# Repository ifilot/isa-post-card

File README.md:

# ISA POST card

8-bit ISA post card for XT-class systems

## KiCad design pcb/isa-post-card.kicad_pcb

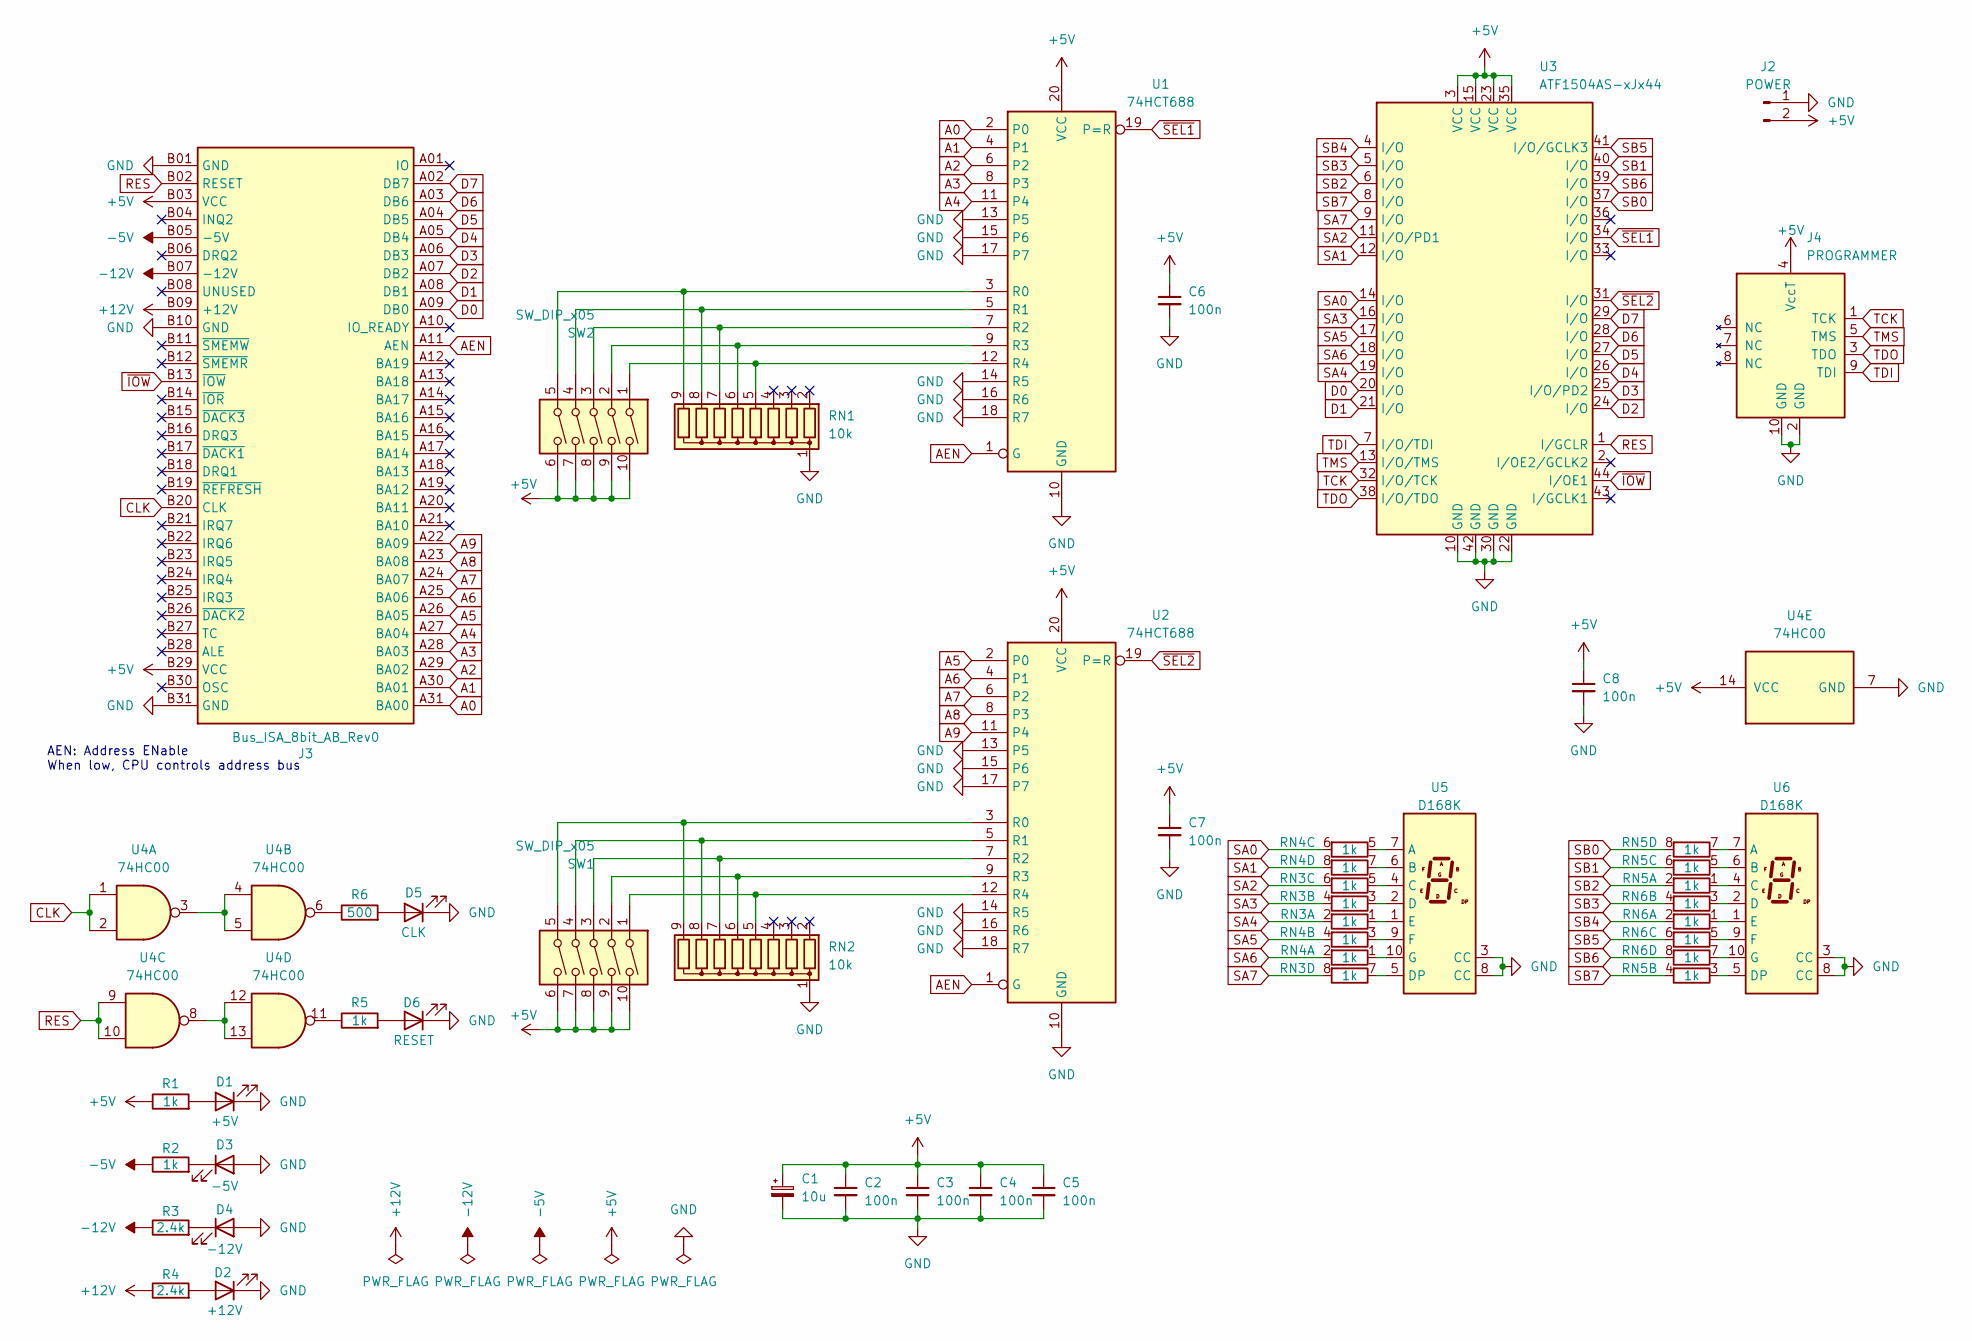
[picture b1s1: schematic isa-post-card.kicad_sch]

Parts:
C1: 10u; CP_Radial_D4.0mm_P1.50mm
C2, C3, C4, C5, C6, C7, C8: 100n; C_Disc_D5.0mm_W2.5mm_P5.00mm
D1: +5V; LED_D5.0mm
D2: +12V; LED_D5.0mm
D3: -5V; LED_D5.0mm
D4: -12V; LED_D5.0mm
D5: CLK; LED_D5.0mm
D6: RESET; LED_D5.0mm
J2: POWER; PinHeader_1x02_P2.54mm_Vertical
J3: Bus_ISA_8bit_AB_Rev0; ISA_CARD_EDGE_CONNECTOR_8BIT_Rev1
J4: PROGRAMMER; IDC-Header_2x05_P2.54mm_Vertical
R1, R2, R5: 1k; R_Axial_DIN0207_L6.3mm_D2.5mm_P7.62mm_Horizontal
R3, R4: 2.4k; R_Axial_DIN0207_L6.3mm_D2.5mm_P7.62mm_Horizontal
R6: 500; R_Axial_DIN0207_L6.3mm_D2.5mm_P7.62mm_Horizontal
RN1, RN2: 10k; R_Array_SIP9
RN3, RN4, RN5, RN6: 1k; R_Array_SIP8
SW1, SW2: SW_DIP_x05; SW_DIP_SPSTx05_Slide_9.78x14.88mm_W7.62mm_P2.54mm
U1, U2: 74HCT688; DIP-20_W7.62mm_Socket
U3: ATF1504AS-xJx44; PLCC-44_THT-Socket
U4: 74HC00; DIP-14_W7.62mm_Socket
U5, U6: D168K; D1X8K

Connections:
+5V: C1.1, C2.1, C3.1, C4.1, C5.1, C6.1, C7.1, C8.1, J2.2, J3.B03 (VCC), J3.B29 (VCC), J4.4 (VccT), R1.1, SW1.6, SW1.7, SW1.8, SW1.9, SW1.10, SW2.6, SW2.7, SW2.8, SW2.9, SW2.10, U1.20 (VCC), U2.20 (VCC), U3.3 (VCC), U3.15 (VCC), U3.23 (VCC), U3.35 (VCC), U4.14 (VCC)
+12V: J3.B09 (+12V), R4.1
-5V: J3.B05 (-5V), R2.1
-12V: J3.B07 (-12V), R3.1
A0: J3.A31 (BA00), U1.2 (P0)
A1: J3.A30 (BA01), U1.4 (P1)
A2: J3.A29 (BA02), U1.6 (P2)
A3: J3.A28 (BA03), U1.8 (P3)
A4: J3.A27 (BA04), U1.11 (P4)
A5: J3.A26 (BA05), U2.2 (P0)
A6: J3.A25 (BA06), U2.4 (P1)
A7: J3.A24 (BA07), U2.6 (P2)
A8: J3.A23 (BA08), U2.8 (P3)
A9: J3.A22 (BA09), U2.11 (P4)
AEN: J3.A11 (AEN), U1.1 (G), U2.1 (G)
CLK: J3.B20 (CLK), U4.1, U4.2
D0: J3.A09 (DB0), U3.20 (I/O)
D1: J3.A08 (DB1), U3.21 (I/O)
D2: J3.A07 (DB2), U3.24 (I/O)
D3: J3.A06 (DB3), U3.25 (I/O/PD2)
D4: J3.A05 (DB4), U3.26 (I/O)
D5: J3.A04 (DB5), U3.27 (I/O)
D6: J3.A03 (DB6), U3.28 (I/O)
D7: J3.A02 (DB7), U3.29 (I/O)
GND: C1.2, C2.2, C3.2, C4.2, C5.2, C6.2, C7.2, C8.2, D1.1 (K), D2.1 (K), D3.2 (A), D4.2 (A), D5.1 (K), D6.1 (K), J2.1, J3.B01 (GND), J3.B10 (GND), J3.B31 (GND), J4.2 (GND), J4.10 (GND), RN1.1 (common), RN2.1 (common), U1.10 (GND), U1.13 (P5), U1.14 (R5), U1.15 (P6), U1.16 (R6), U1.17 (P7), U1.18 (R7), U2.10 (GND), U2.13 (P5), U2.14 (R5), U2.15 (P6), U2.16 (R6), U2.17 (P7), U2.18 (R7), U3.10 (GND), U3.22 (GND), U3.30 (GND), U3.42 (GND), U4.7 (GND), U5.3 (CC), U5.8 (CC), U6.3 (CC), U6.8 (CC)
unnamed: D1.2 (A), R1.2
unnamed: D2.2 (A), R4.2
unnamed: D3.1 (K), R2.2
unnamed: D4.1 (K), R3.2
unnamed: D5.2 (A), R6.2
unnamed: D6.2 (A), R5.2
unnamed: R5.1, U4.11
unnamed: R6.1, U4.6
unnamed: RN1.5 (R4), SW2.1, U1.12 (R4)
unnamed: RN1.6 (R5), SW2.2, U1.9 (R3)
unnamed: RN1.7 (R6), SW2.3, U1.7 (R2)
unnamed: RN1.8 (R7), SW2.4, U1.5 (R1)
unnamed: RN1.9 (R8), SW2.5, U1.3 (R0)
unnamed: RN2.5 (R4), SW1.1, U2.12 (R4)
unnamed: RN2.6 (R5), SW1.2, U2.9 (R3)
unnamed: RN2.7 (R6), SW1.3, U2.7 (R2)
unnamed: RN2.8 (R7), SW1.4, U2.5 (R1)
unnamed: RN2.9 (R8), SW1.5, U2.3 (R0)
unnamed: RN3.1 (R1.1), U5.1 (E)
unnamed: RN3.3 (R2.1), U5.2 (D)
unnamed: RN3.5 (R3.1), U5.4 (C)
unnamed: RN3.7 (R4.1), U5.5 (DP)
unnamed: RN4.1 (R1.1), U5.10 (G)
unnamed: RN4.3 (R2.1), U5.9 (F)
unnamed: RN4.5 (R3.1), U5.7 (A)
unnamed: RN4.7 (R4.1), U5.6 (B)
unnamed: RN5.1 (R1.1), U6.4 (C)
unnamed: RN5.3 (R2.1), U6.5 (DP)
unnamed: RN5.5 (R3.1), U6.6 (B)
unnamed: RN5.7 (R4.1), U6.7 (A)
unnamed: RN6.1 (R1.1), U6.1 (E)
unnamed: RN6.3 (R2.1), U6.2 (D)
unnamed: RN6.5 (R3.1), U6.9 (F)
unnamed: RN6.7 (R4.1), U6.10 (G)
unnamed: U4.3, U4.4, U4.5
unnamed: U4.8, U4.12, U4.13
RES: J3.B02 (RESET), U3.1 (I/GCLR), U4.9, U4.10
SA0: RN4.6 (R3.2), U3.14 (I/O)
SA1: RN4.8 (R4.2), U3.12 (I/O)
SA2: RN3.6 (R3.2), U3.11 (I/O/PD1)
SA3: RN3.4 (R2.2), U3.16 (I/O)
SA4: RN3.2 (R1.2), U3.19 (I/O)
SA5: RN4.4 (R2.2), U3.17 (I/O)
SA6: RN4.2 (R1.2), U3.18 (I/O)
SA7: RN3.8 (R4.2), U3.9 (I/O)
SB0: RN5.8 (R4.2), U3.37 (I/O)
SB1: RN5.6 (R3.2), U3.40 (I/O)
SB2: RN5.2 (R1.2), U3.6 (I/O)
SB3: RN6.4 (R2.2), U3.5 (I/O)
SB4: RN6.2 (R1.2), U3.4 (I/O)
SB5: RN6.6 (R3.2), U3.41 (I/O/GCLK3)
SB6: RN6.8 (R4.2), U3.39 (I/O)
SB7: RN5.4 (R2.2), U3.8 (I/O)
TCK: J4.1 (TCK), U3.32 (I/O/TCK)
TDI: J4.9 (TDI), U3.7 (I/O/TDI)
TDO: J4.3 (TDO), U3.38 (I/O/TDO)
TMS: J4.5 (TMS), U3.13 (I/O/TMS)
~IOW: J3.B13 (~IOW), U3.44 (I/OE1)
~SEL1: U1.19 (P=R), U3.34 (I/O)
~SEL2: U2.19 (P=R), U3.31 (I/O)

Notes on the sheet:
AEN: Address ENable When low, CPU controls address bus

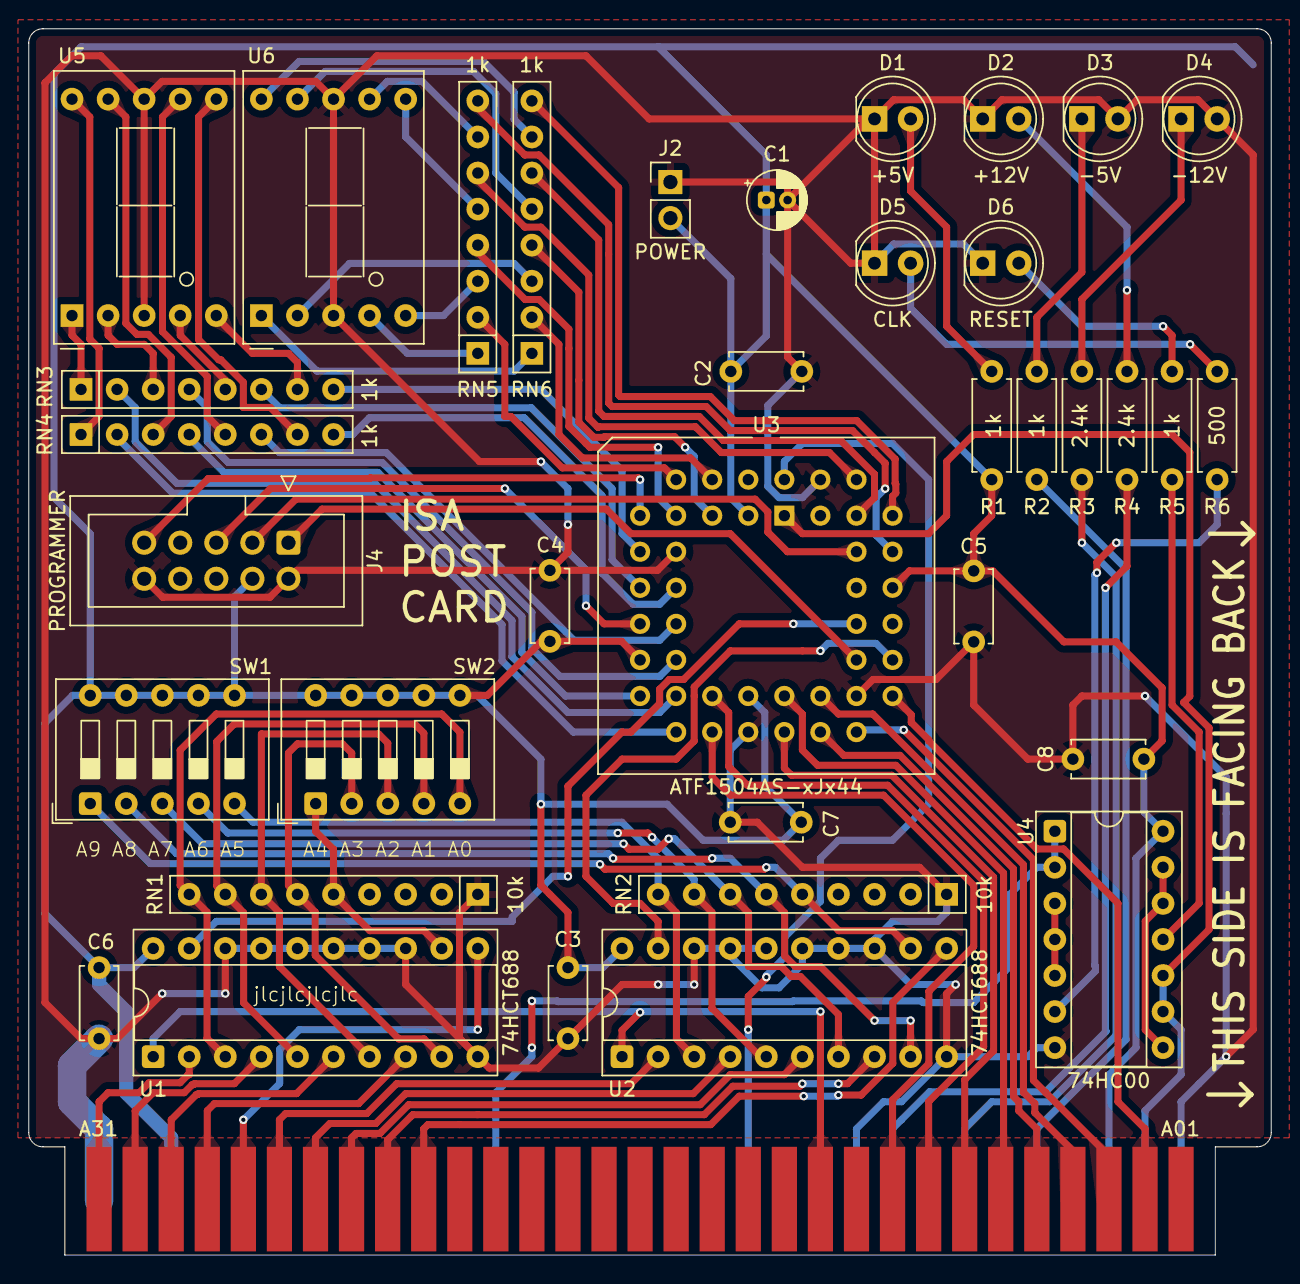
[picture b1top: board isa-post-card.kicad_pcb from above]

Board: 2 copper layers, 87.5 x 86.4 mm, 37 parts (0 on the bottom side), 85 nets.

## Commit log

2025-08-18 Fixing design bugs and adding CUPL code
2025-08-18 Fixing board wiring
2025-08-20 Revising design
2025-09-29 Revising schematics
